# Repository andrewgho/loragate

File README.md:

# loragate - outdoor LoRA radio gate sensor

A battery-powered outdoor door/gate sensor that reports open, close, and
"still open" events over LoRa to an always-on receiver, which forwards
them to a WiFi-connected monitoring server.

## Requirements

- Report door open and close events at medium range, through walls and trees.
- Never miss a door state change, even across resets or transient failures.
- Multi-year battery life on primary lithium cells in a warm outdoor climate.

## Implementation pieces

- **[`tx`](tx/)** — outdoor transmitter: XIAO ESP32-C6 + Wio-SX1262,
  reed switch, 3x AA lithium cells. Deep-sleeps between events.
- **[`rx`](rx/)** — indoor receiver: same radio hardware, but USB-powered,
  always on, and WiFi connected. Listens for and acks transmissions from `tx`,
  forwards events to a monitoring server over HTTP, and lights an LED beacon.
- **[`test/`](test/)** — host-side tests (no ESP32 toolchain needed) for the
  parts of `tx`/`rx` written to be testable without hardware: the wire
  format, `tx`'s wake-decision logic, and `rx`'s retry-dedup logic.

## Why these choices

**LoRa for the transmitter.** WiFi and BLE are too expensive power wise.
Z-wave or Zigbee was empirically proven to not be able to transmit through
walls and low-E window coatings in my particular home setting. LoRA radio
has super low power requirements and has excellent range for my use case.

**XIAO ESP32-C6, deep-sleep by default, event-driven wake.** The outdoor
unit is battery powered, with the goal of 2+ years of battery life. The `tx`
unit deep-sleeps and wakes only on a reed-switch edge change or a backstop
RTC timer (see "Software" below), using the C6's RTC domain and `RTC_NOINIT_ATTR` memory to store state between wakes.

**Primary AA lithium cells through an LDO.** The outdoor enclosure is sealed
in a northern Californian climate which can get warm (up to 90°F ambient),
so Li-ion/LiPo rechargeable cells were rejected for safety reasons (spicy
battery). Consumer-available primary AA lithium cells (Energizer L91 or
equivalent) are rated up to 140°F and have inbuilt protections. An LDO with
low quiescent power draw and a PTC fuse protect against voltage fluctuation
over time and short circuits, respectively. See the Transmitter "Power"
section of [`WIRING.md`](WIRING.md) for details and alternatives considered.

**Simple ack/retry over the radio link.** For maximum simplicity, this is a
point to point LoRA protocol, where each event is one small packet (type +
sequence number + retry count); `tx` retries with backoff until `rx` acks it
or it gives up. The radio link is empirically clean so we do not need the
complexity of a meshed protocol.

**Wake/sleep decision logic is pure C++, separate from Arduino/radio code.**
`tx/door_wake_logic.h` decides what a wake means and what should do with no
Arduino, radio, or Serial dependencies. `tx/tx.ino` is just the I/O shell that
reads the pin and carries out the decision. That split lets us run unit tests
in `test/test_tx_wake_logic.cpp` to exercise the actual decision rules,
including regression cases for real bugs caught along the way (see "History"
below) with a plain C++ compiler, no hardware required.

### Power budget

The overall goal for the battery-powered transmitter is 2+ years between
battery changes. With the chosen components, the deep-sleep current was
measured on a Nordic PPK2 is as follows:

| Source | Current |
|---|---|
| Deep sleep, door closed | **21.9µA** |
| Deep sleep, door open | **18.5µA** |
| Active transmit (~120ms burst, +22dBm) | **~125mA** |

Budgeting conservatively for ~54 radio events/day (20 door transitions, an hourly heartbeat, and occasional held-open checks, see "Software" below)
against ~2,100mAh realistically extractable from a 3x AA L91 pack:

```
sleep:  0.0219mA * 24h             ≈ 0.526 mAh/day
active: 54 * 0.120s * 125mA / 3600 ≈ 0.225 mAh/day
total                              ≈ 0.751 mAh/day
2,100 mAh / (0.751 mAh/day * 365)  ≈ 7.7 years
```

In real life, temperature, battery degradation, and other factors will likely
bring the battery life down from the calculated figure, but we should be
comfortably over the "2+ years" bar.

### History

This and other History sections are AI authored, and contain the lessons
learned during iteration, with the hope of not repeating any false starts.

- The project's first draft (an AI-authored plan, not hardware-checked)
  got real things wrong: a reed-switch pin that collided with the
  radio's own NSS pin, and a direct battery-to-`3V3` connection with no
  margin against the chip's voltage ceiling. Both forced real design
  changes — see WIRING.md's Transmitter pin table and LDO section.
- The transmit-current figure was off by more than 3x for a while
  (~35mA assumed vs. ~120-125mA actual) until it was checked against
  the SX1262 and Wio-SX1262 module datasheets directly.
- Deep-sleep current measured ~1.5mA on the first PPK2 pass — ~40x the
  budget. Root cause took two parts: the SX1262 wakes itself from
  SLEEP on an NSS falling edge, and the ESP32-C6 doesn't hold a GPIO's
  level across sleep unless told to (fixed with `gpio_hold_en()`); and
  the Wio-SX1262 HAT's own onboard button shares the reed switch's
  `D0` net with a pull-up that drew current whenever the door was
  closed (confirmed against Seeed's schematic, fixed by bypassing `D0`
  around the HAT in hardware — see WIRING.md). Final measured number
  is the 21.9µA/18.5µA above.
- A `while (!Serial)` wait-for-USB-monitor loop in `tx`'s `setup()`
  burned up to 3 seconds of fully-awake CPU time on every single wake
  in the field — a real battery-life cost, not just a latency
  annoyance — because deep sleep drops the USB peripheral and nothing
  was ever there to satisfy the wait. Fixed by gating it behind
  `-DDEBUG`.

## Hardware

Both nodes use the same radio hardware — a Seeed XIAO ESP32-C6 paired
with a Seeed Wio-SX1262 (the "for XIAO ESP32S3" through-hole-header
variant; Seeed doesn't sell this exact pairing, so the pinout is
confirmed against the physical boards, not a datasheet — see
WIRING.md's "Shared radio stack"), each with the small ribbon antenna
that ships with the Wio-SX1262. What differs is what's attached, how
each is powered, and what the modules mount on.

This section covers what the pieces are and why; **WIRING.md has the
full pin tables, part numbers/links, and physical build/wiring
instructions**, in matching Transmitter/Receiver sections — that's the
doc to open to actually order parts or wire up a unit.

### Transmitter

Reed switch on `D0` (the only free deep-sleep-wake-capable pin), 3x AA
lithium pack through an LDO and a PTC fuse, on a custom KiCad PCB
(`kicad/`) in an IP65 enclosure with the antenna inside. No USB power
in the field. The PCB doesn't stack the modules as a HAT: it seats them
side by side, with the Wio flipped on its back for easier routing. That
lets it leave the Wio's `D0` unconnected, which isolates the reed
switch from the HAT's onboard button without modifying either module.
A UART header on D6/D7 takes an FTDI adapter for production-build
serial monitoring. A 3D-printed mount (`mount/`) holds the PCB and
battery holder in the enclosure. (The original Perma-Proto protoboard
build is still documented in WIRING.md.)

### Receiver

USB-powered, indoors, no battery or enclosure concerns — it just needs
to stay on and stay on WiFi. The usual XIAO + Wio HAT stack plugs into
a 1"x1" protoboard wired as a dual 7-pin socket, which also carries
the one peripheral: a small 5V LED rotating beacon, lit while the gate
is held open, switched from `D0` by a low-side logic-level MOSFET.

### History

- The Wio-SX1262's pinout for this XIAO had to be read off the boards'
  silkscreen — an earlier schematic-derived guess was off by one
  header position and failed radio init outright
  (`RADIOLIB_ERR_CHIP_NOT_FOUND`).
- The transmitter's first LDO pick (TI TPS7A0233, true nanopower) had
  a dead bench unit (0V output, bad part or solder joint, not a design
  issue); the MCP1700 — higher quiescent current, but simpler to build
  and confirmed working — is what's actually installed. TPS7A0233
  remains a documented alternative if a working unit gets built later.
  See WIRING.md's "Choosing an LDO".
- The Wio-SX1262 HAT's own onboard button turned out to share the
  reed switch's `D0` net (see "Power budget" → "History" above) — a
  hardware quirk of the stacked-header build, not something visible
  from either board's datasheet alone. The protoboard build fixed it by
  snipping `D0` out of the stack; the PCB avoids it by design.
- The battery disconnect moved from JST-PH 2.0mm to Molex KK-254-style
  (2.54mm, generic KF2510 kit parts): JST-PH crimp pins aren't
  practical to crimp at home, and KK-254-style ones are.
- Long-range SMA antennas (with U.FL-to-bulkhead pigtails) were bought
  for both nodes. The Wio-SX1262's stock ribbon antenna turned out to
  give enough range, so both nodes use that: it fits inside the
  enclosure and takes up little room.
- The receiver's beacon was first wired to `D6`, reasoning that rx's
  `Serial` runs over native USB so UART0's pins were free. The gate sat
  at ~3V whatever the firmware wrote. Root cause, confirmed against the
  installed core's sdkconfig rather than a web search: the prebuilt
  ESP-IDF has its console on UART0 regardless of `CDCOnBoot` (an SDK
  configuration choice, not a silicon limit, as an earlier draft
  wrongly claimed). Moved to `D0`. `D7` is ruled out for the same
  reason.
- After the move to `D0`, the gate read a steady ~1.6V and the beacon
  stayed off. That's almost exactly the divider voltage for an
  *undriven* `D0` (the HAT's 10kΩ pull-up against the beacon's
  220Ω+10kΩ pulldown). The cause was the macOS flashing box's stale
  checkout, still flashing the `D6` build. A pull and reflash fixed it,
  with no hardware change. Check `git pull` before chasing an
  electrical-looking symptom.
- The beacon was first planned on a separate standalone protoboard,
  wired to the stack through a pair of 1x3 headers. That layout's first
  draft landed the GND→Source jumper on the `D0` island instead of a
  GND one, which would have tied `D0` straight to the MOSFET source.
  It was caught in review, before soldering, by tracing each hole
  against the header assignment rather than trusting the layout's
  prose labels. The as-built board instead puts the circuit on the
  protoboard that sockets the stack, with a 2-pin output header.
- The beacon circuit's flyback diode was dropped after a PPK2
  measurement showed the beacon is LED-only, not motor-driven.

## Software

### Transmitter (`tx/`)

Deep sleeps by default. Each wake runs `setup()` once (there's no
persistent `loop()`), decides what — if anything — to send, and goes
back to sleep from inside that decision:

- Wakes on a reed-switch edge, or an RTC timer backstop that's always
  armed (a short one while an open episode hasn't yet been
  re-verified, a long hourly one otherwise).
- Every wake diffs the real pin state against a persisted "last
  reported" baseline — whether something changed is never inferred
  from *why* the chip woke up, only from that diff. A real edge that
  settles back to the same state (reed-switch bounce/chatter outdoors)
  is told apart from a genuinely elapsed timer and sent nothing.
- A door transition is reported immediately; a door left open past a
  threshold gets one follow-up "still open" check (not a repeating
  one); anything else falls back to an hourly heartbeat floor so
  silence never goes on indefinitely.
- The handful of values that need to survive both sleep *and* a
  restart (sequence counter, last-reported door state, a pending
  reset-diagnostic flag) live in `RTC_NOINIT_ATTR` memory, validated
  by a checksum (`tx/rtc_checksum.h`) since that memory section isn't
  zeroed by the bootloader the way `RTC_DATA_ATTR` would be.
- An abnormal boot/reset reason (anything other than a routine
  deep-sleep wake or the transmitter's own restart) gets reported as a
  diagnostic packet, detected before the radio is even brought up so
  it isn't lost if `radio.begin()` happens to fail on that particular
  wake.
- The wake-decision rules themselves live in `tx/door_wake_logic.h` —
  see "Why these choices" above for why that's a separate, pure file.

### Receiver (`rx/`)

Always on, always listening:

- Acks every recognized packet (so `tx` stops retrying) and dedups by
  sequence number before acting on it, since an ack-loss retry resends
  the same event.
- Forwards door open/close/heartbeat/held-open/diagnostic events to a
  monitoring server over HTTP (URLs and WiFi credentials in
  `rx/local.h` — see "Build, test, and flash").
- Joins WiFi under `RX_HOSTNAME` (DHCP hostname, so the router shows it
  and serves local DNS for it) and advertises it over mDNS as
  `<name>.local`.
- Drives the held-open beacon through `beacon_should_be_on()`. For now
  it's lit whenever the door's open (testing phase); the intended final
  behavior, lit only after a held-open alert fires, is a one-line
  change there.
- Runs its own lightweight checks independent of what the transmitter
  decides to send: a faster local "door open past 45s" alert, a
  "haven't heard from the transmitter in a while" staleness alert, and
  proactive WiFi reconnect if the connection drops.

### Wire protocol

One packet type covers acks (`PKT_ACK`); the rest cover transmitter
events (`PKT_HEARTBEAT`, `PKT_DOOR_OPEN`, `PKT_DOOR_CLOSE`,
`PKT_DOOR_HELD_OPEN`, `PKT_DIAGNOSTIC`) — see `lora_packet.h` (kept
byte-identical between `tx/` and `rx/`, checked by `make test`) for
the exact struct. `tx` sends, waits for a matching ack, and retries
with backoff (capped attempts) before giving up on that one event.

### Build, test, and flash

Toolchain: [`arduino-cli`](https://arduino.github.io/arduino-cli/) with
the ESP32 board package, plus the RadioLib library:

```sh
arduino-cli lib install RadioLib
```

From the repo root:

- `make compile` — compiles `tx/` and `rx/` against the installed
  ESP32 core + RadioLib. No upload, no hardware needed.
- `make test` — host-side tests (`test/`), no ESP32 toolchain needed
  at all, just a C++ compiler. Covers the wire format and the pure
  logic described above; **does not** reach actual hardware behavior
  (real deep sleep, a real reed-switch edge, radio range, WiFi/HTTP) —
  only flashing a real board confirms those.
- `make flash-tx` / `make flash-rx` — flash `tx`/`rx`.

Each sketch directory also has its own `Makefile` (`make flash`,
`make debug`, `make monitor`, `make clean`). `make debug` substitutes
a `delay()`+restart loop for deep sleep so USB/serial stays up for
monitoring, and builds with `-DDEBUG` (enables verbose logging and,
on `tx`, the wait-for-monitor loop that production builds skip — see
"History" below).

`rx/` needs `rx/local.h` (gitignored) for WiFi credentials and the
HTTP URL templates it forwards events to — copy `rx/local.h.example`
and fill it in. `tx/` needs no `local.h` (no WiFi).

### History

- The transmitter's wakeup source was originally planned as
  `esp_sleep_enable_ext0_wakeup()`; the ESP32-C6 doesn't implement
  ext0 at all. `esp_sleep_enable_ext1_wakeup()` (a GPIO bitmask, not a
  pin number) replaced it.
- A live brownout-looking symptom (rapid door toggling occasionally
  dropped an event and reset the sequence counter to 0) turned out to
  be a real persistence bug, not a hardware brownout: `RTC_DATA_ATTR`
  is only documented to survive deep sleep, not `ESP.restart()`
  (the rapid-slam/bounce guard's own restart) — switching to
  `RTC_NOINIT_ATTR` plus a checksum fixed it.
- A reed-switch edge that bounces back to the same debounced state
  (wind/vibration on an outdoor gate) was originally indistinguishable
  from a genuinely elapsed timer, so it could burn an unneeded
  heartbeat or consume the one-shot held-open check's budget early.
  Fixed by checking the actual wakeup cause, but only in the
  already-no-transition branches.
- If `radio.begin()` ever failed on the very first wake after a true
  power-on, a later successful wake could silently adopt whatever the
  door happened to be doing *then* as the starting baseline — losing
  any real transition that happened in between with no event ever
  sent. Fixed by establishing the baseline from the pin alone, before
  the radio is even touched.
- The held-open check originally re-armed every interval for as long
  as the door stayed open (~280 wakes/day for a day-long open door);
  made one-shot per open episode instead.
- An ack-loss retry (receiver got and acked the original fine, but the
  ack itself got lost) was double-notifying the monitoring server for
  the same event; fixed by dedup-by-sequence-number on the receiver
  before acting on a packet, while still acking unconditionally.
- The receiver's "transmitter's gone quiet" staleness alert originally
  cleared its one-shot latch on *any* radio reception, including a
  CRC failure — caught live when CRC failures logged while the
  transmitter was confirmed powered off overnight suppressed the
  alert that should have kept firing. Fixed by only clearing the
  latch on a reception that actually decodes as a known packet type
  (the silence *clock* still resets on any reception, since that part
  was never wrong).
- NTP sync and a reported `localtime=` field were added, then removed:
  the actual timing gap they were meant to close (radio-level latency)
  is usually under a second and gets swamped by the monitoring
  channel's own latency anyway — not worth the added wire-format and
  firmware complexity.

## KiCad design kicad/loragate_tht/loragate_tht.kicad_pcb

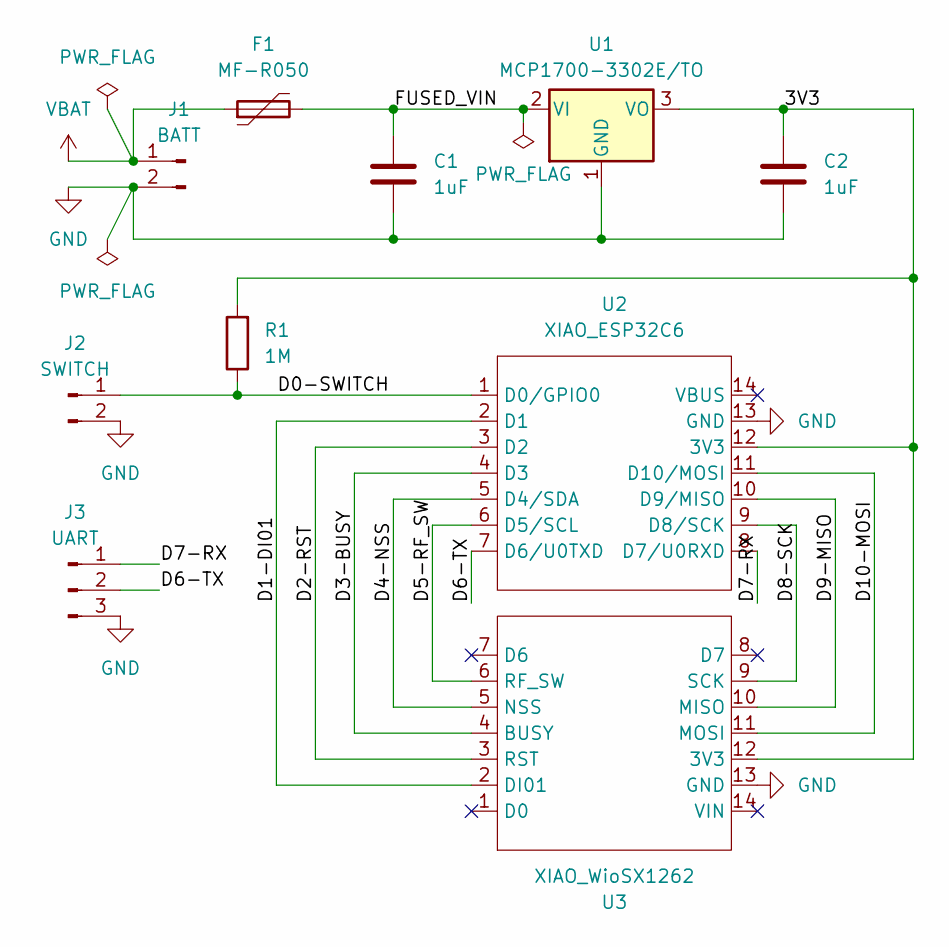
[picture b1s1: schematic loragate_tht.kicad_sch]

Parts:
C1, C2: 1uF; C_Disc_D5.0mm_W2.5mm_P5.00mm
F1: MF-R050; C_Disc_D8.0mm_W2.5mm_P5.00mm
J1: BATT; Molex_KK-254_AE-6410-02A_1x02_P2.54mm_Vertical
J2: SWITCH; PinHeader_1x02_P2.54mm_Vertical
J3: UART; PinHeader_1x03_P2.54mm_Vertical
R1: 1M; R_Axial_DIN0207_L6.3mm_D2.5mm_P10.16mm_Horizontal
U1: MCP1700-3302E/TO; TO-92_Inline_Wide
U2: XIAO_ESP32C6; XIAO_Module_Socket_2x7_P2.54mm_W15.24mm
U3: XIAO_WioSX1262; XIAO_Module_Pin_Flipped_2x7_P2.54mm_W15.24mm

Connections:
/3V3: C2.1, R1.2, U1.3 (VO), U2.12 (3V3), U3.12 (3V3)
/D0-SWITCH: J2.1, R1.1, U2.1 (D0/GPIO0)
/D1-DI01: U2.2 (D1), U3.2 (DI01)
/D2-RST: U2.3 (D2), U3.3 (RST)
/D3-BUSY: U2.4 (D3), U3.4 (BUSY)
/D4-NSS: U2.5 (D4/SDA), U3.5 (NSS)
/D5-RF_SW: U2.6 (D5/SCL), U3.6 (RF_SW)
/D6-TX: J3.2, U2.7 (D6/U0TXD)
/D7-RX: J3.1, U2.8 (D7/U0RXD)
/D8-SCK: U2.9 (D8/SCK), U3.9 (SCK)
/D9-MISO: U2.10 (D9/MISO), U3.10 (MISO)
/D10-MOSI: U2.11 (D10/MOSI), U3.11 (MOSI)
/FUSED_VIN: C1.1, F1.2, U1.2 (VI)
GND: C1.2, C2.2, J1.2, J2.2, J3.3, U1.1 (GND), U2.13 (GND), U3.13 (GND)
VBAT: F1.1, J1.1

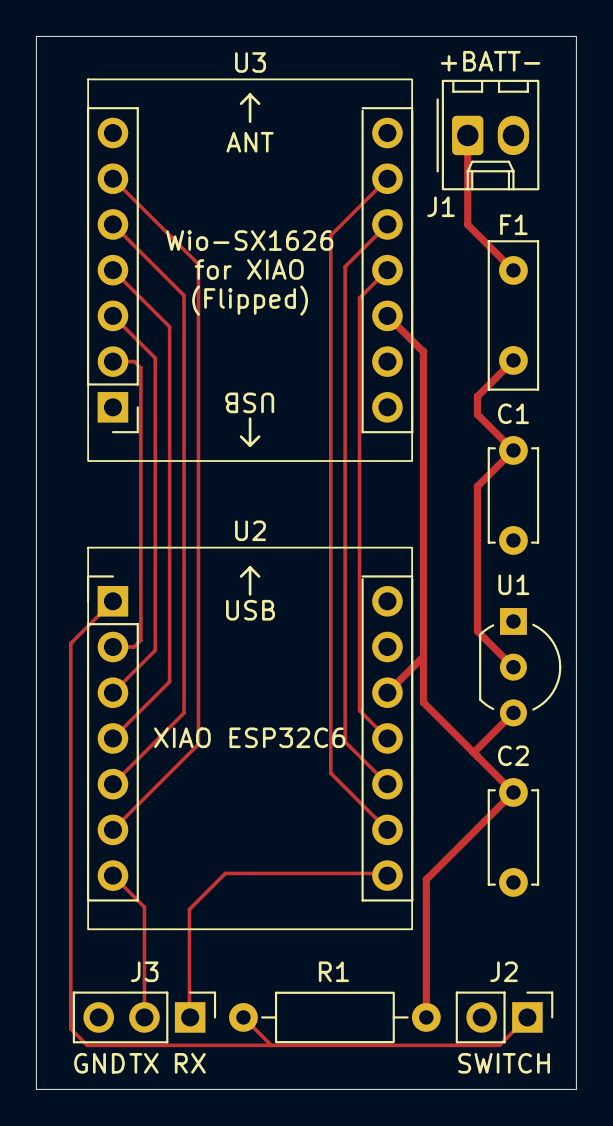
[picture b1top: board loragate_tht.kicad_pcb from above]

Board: 2 copper layers, 30.0 x 58.5 mm, 10 parts (0 on the bottom side), 15 nets.
